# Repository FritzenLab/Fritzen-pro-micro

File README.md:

# Fritzen-pro-micro
 a dev board based on the Arduino Pro micro

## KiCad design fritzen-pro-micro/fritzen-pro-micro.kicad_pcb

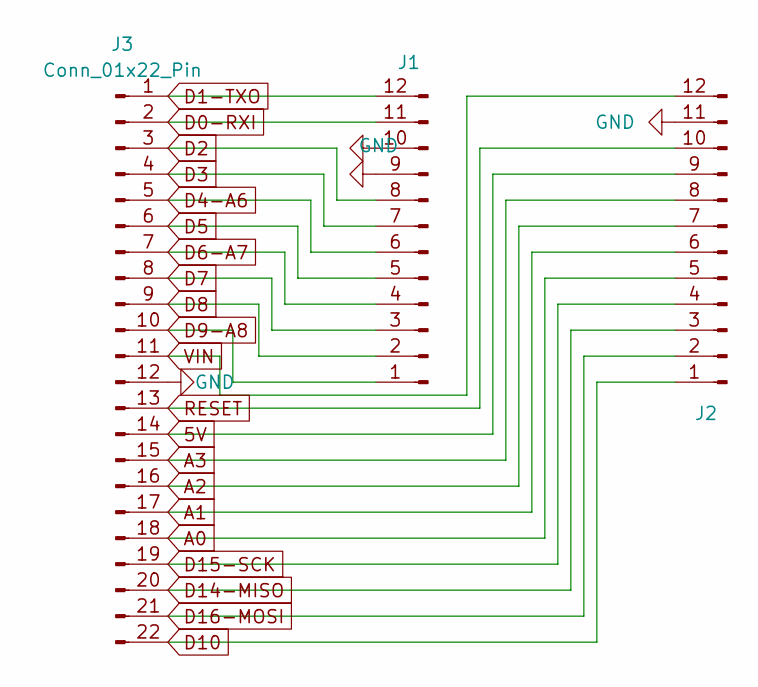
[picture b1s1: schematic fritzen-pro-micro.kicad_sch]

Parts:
J1, J2: Conn_01x12_Pin; PinHeader_1x12_P2.54mm_Vertical
J3: Conn_01x22_Pin; PinHeader_1x22_P2.54mm_Vertical

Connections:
5V: J2.9, J3.14
A0: J2.5, J3.18
A1: J2.6, J3.17
A2: J2.7, J3.16
A3: J2.8, J3.15
D0-RXI: J1.11, J3.2
D1-TXO: J1.12, J3.1
D2: J1.8, J3.3
D3: J1.7, J3.4
D4-A6: J1.6, J3.5
D5: J1.5, J3.6
D6-A7: J1.4, J3.7
D7: J1.3, J3.8
D8: J1.2, J3.9
D9-A8: J1.1, J3.10
D10: J2.1, J3.22
D14-MISO: J2.3, J3.20
D15-SCK: J2.4, J3.19
D16-MOSI: J2.2, J3.21
GND: J1.9, J1.10, J2.11, J3.12
RESET: J2.10, J3.13
VIN: J2.12, J3.11

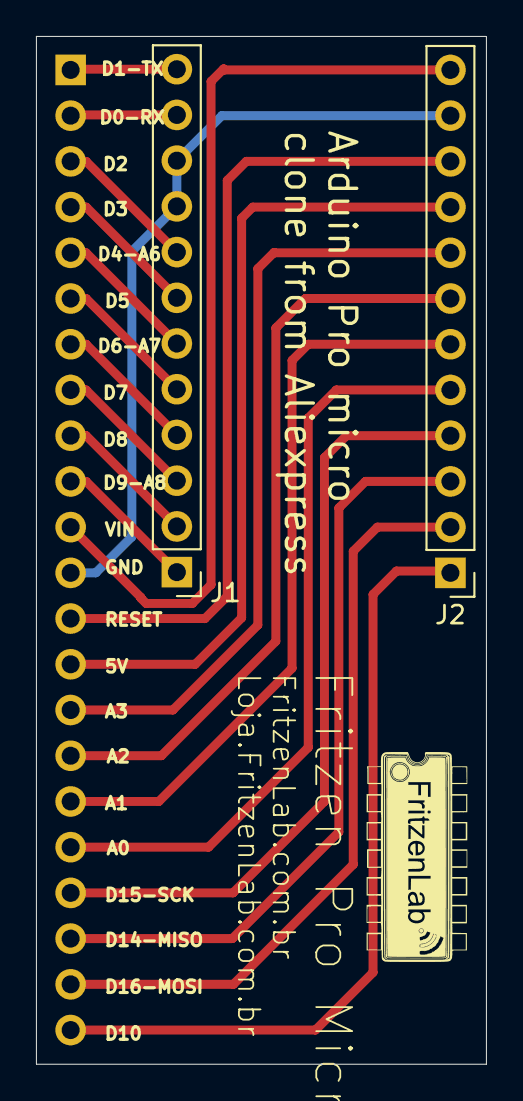
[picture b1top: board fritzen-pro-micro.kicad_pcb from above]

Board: 2 copper layers, 25.0 x 57.1 mm, 3 parts (1 on the bottom side), 22 nets.

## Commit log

2024-11-06 added schematics
2024-11-06 edited schematics
2024-11-06 Started layouting
2024-11-06 backups
2024-11-06 edited PCB
2024-11-07 finished design, generated gerber
